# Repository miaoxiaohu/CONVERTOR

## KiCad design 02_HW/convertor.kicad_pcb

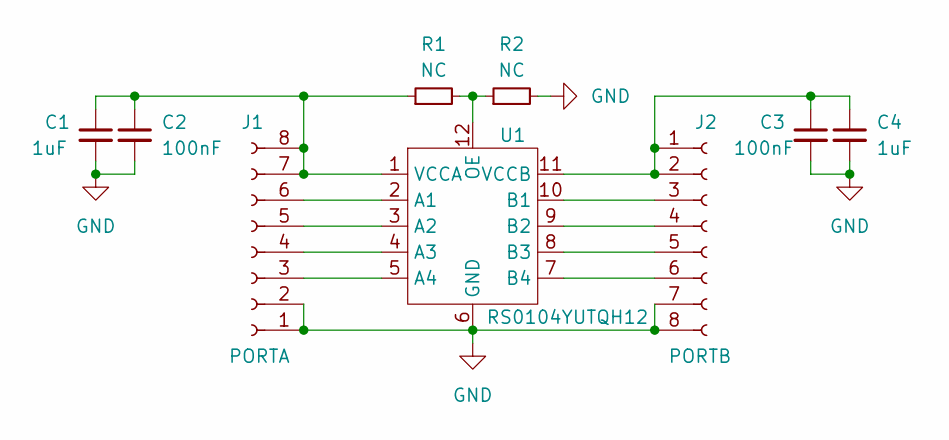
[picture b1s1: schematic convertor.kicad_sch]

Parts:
C1, C4: 1uF; C_0603_1608Metric
C2, C3: 100nF; C_0402_1005Metric
J1: PORTA; PinHeader_1x08_P2.54mm_Horizontal
J2: PORTB; PinHeader_1x08_P2.54mm_Horizontal
R1, R2: NC; R_0402_1005Metric
U1: RS0104YUTQH12; QFN2x1.7-12L

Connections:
GND: C1.2, C2.2, C3.2, C4.2, J1.1, J1.2, J2.7, J2.8, R2.2, U1.6 (GND)
unnamed: C1.1, C2.1, J1.7, J1.8, R1.1, U1.1 (VCCA)
unnamed: C3.1, C4.1, J2.1, J2.2, U1.11 (VCCB)
unnamed: J2.3, U1.10 (B1)
unnamed: J2.4, U1.9 (B2)
unnamed: J2.5, U1.8 (B3)
unnamed: J2.6, U1.7 (B4)
unnamed: R1.2, R2.1, U1.12 (OE)
unnamed: J1.6, U1.2 (A1)
unnamed: J1.5, U1.3 (A2)
unnamed: J1.4, U1.4 (A3)
unnamed: J1.3, U1.5 (A4)

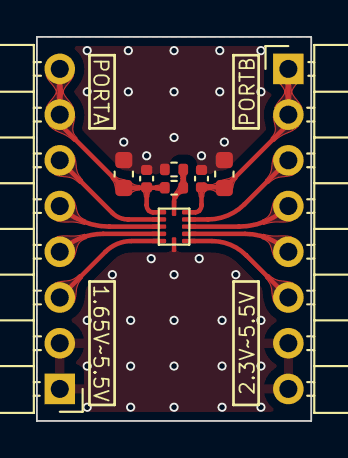
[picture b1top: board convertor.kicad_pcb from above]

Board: 2 copper layers, 15.2 x 21.3 mm, 9 parts (0 on the bottom side), 12 nets.

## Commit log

2022-07-07 上传PCB文件
